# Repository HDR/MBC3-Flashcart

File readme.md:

# Make sure you read the [LICENSE](https://github.com/HDR/MBC3-Flashcart/blob/master/LICENSE)

MBC3 Flashcart based on retroreboot's cartridge that uses 0603 components (while based on the RetroReboot carts, these are completely redesigned from the ground up in kicad)

If you want a 4MB cart check out my new [MBC30 flashcart repo](https://github.com/HDR/MBC30-Flashcart)

Version 1.5 and beyond makes use of [djedditt's](https://github.com/djedditt/) [cartridge connector footprint](https://github.com/djedditt/kicad-gamepaks)

**PCBWay:**

As a disclaimer, i get 10% kickback on shared pcbway orders, if you want the cheaper option go with either JLCPCB or OshPark

If you want to support me for free (and get 5 USD in new user credit) you can use my PCBWay [Referral link](https://www.pcbway.com/setinvite.aspx?inviteid=388393) when signing up on PCBWay

**OSHPark:**

[Purchase on OSHPARK](https://oshpark.com/shared_projects/YCtVNv4A)

Make sure to select the "2 oz copper, 0.8mm thickness" option before checkout

**JLCPCB:**

Upload gerbers(.zip files) to [JLCPCB](http://jlcpcb.com)

Make sure you order with the following settings:

PCB Thickness: 0.8

PCB Color: Any

Surface Finish: ENIG-RoHS

Gold Fingers: Yes (45° chamfered border)

Castellated Holes: No

Check out the [Interactive BOM](https://hdr.github.io/ibom/MBC3-Flashcart) for an interactive website that lets you keep track of where everything goes.

## BOM

| Reference        | Part Number           | Description  | Package |
| :-------------: |:-------------:| :-----:| :-----:|
| U1 | AM29F016(2MB)/AM29F032(4MB)/MBM29F033C(4MB) | 2/4MB Flash Chip | TSOP-48/TSOP-40 |
| U2 | MBC3 | Get from real cartridge | LQFP-32 |
| U3 | FM18W08 | 256kbit FRAM | SOIC-28 |
| U4 | BA6129AF | Buy or get from real cartridge | SOIC-8 |
| U5 | [74LVC1G332GV,125](https://www.nexperia.com/products/analog-logic-ics/control-logic/gates/or-gates/74LVC1G332GV.html) | 3-input OR gate | TSOP-6 |
| C1 | [CL10B104KO8NNNC](https://lcsc.com/product-detail/Multilayer-Ceramic-Capacitors-MLCC-SMD-SMT_Samsung-Electro-Mechanics-CL10B104KO8NNNC_C66501.html)* | 100nF Capacitor | 0603 |
| C2 | [CL10B104KO8NNNC](https://lcsc.com/product-detail/Multilayer-Ceramic-Capacitors-MLCC-SMD-SMT_Samsung-Electro-Mechanics-CL10B104KO8NNNC_C66501.html)* | 100nF Capacitor | 0603 |
| C3 | [CL10B104KO8NNNC](https://lcsc.com/product-detail/Multilayer-Ceramic-Capacitors-MLCC-SMD-SMT_Samsung-Electro-Mechanics-CL10B104KO8NNNC_C66501.html)* | 100nF Capacitor | 0603 |
| C4 | [CL10C150JB8NNNC](https://lcsc.com/product-detail/Multilayer-Ceramic-Capacitors-MLCC-SMD-SMT_Samsung-Electro-Mechanics-CL10C150JB8NNNC_C1644.html)* | 15pF Capacitor | 0603 |
| C5 | [CL10C150JB8NNNC](https://lcsc.com/product-detail/Multilayer-Ceramic-Capacitors-MLCC-SMD-SMT_Samsung-Electro-Mechanics-CL10C150JB8NNNC_C1644.html)* | 15pF Capacitor | 0603 |
| C6 | [CL10B104KO8NNNC](https://lcsc.com/product-detail/Multilayer-Ceramic-Capacitors-MLCC-SMD-SMT_Samsung-Electro-Mechanics-CL10B104KO8NNNC_C66501.html)* | 100nF Capacitor | 0603 | 0603 |
| C7 | [CL10B104KO8NNNC](https://lcsc.com/product-detail/Multilayer-Ceramic-Capacitors-MLCC-SMD-SMT_Samsung-Electro-Mechanics-CL10B104KO8NNNC_C66501.html)* | 100nF Capacitor | 0603 |
| R1 | [RC0603FR-07330KL](https://lcsc.com/product-detail/Chip-Resistor-Surface-Mount_YAGEO-RC0603FR-07330KL_C114618.html)* | 330K Ω Resistor | 0603 |
| R2 | [RC0603FR-0710KL](https://lcsc.com/product-detail/Chip-Resistor-Surface-Mount_YAGEO-RC0603FR-0710KL_C98220.html)* | 10K Ω Resistor | 0603 |
| R3 | [RC0603FR-071KL](https://lcsc.com/product-detail/Chip-Resistor-Surface-Mount_YAGEO-RC0603FR-071KL_C22548.html)* | 1K Ω Resistor | 0603 |
| SW1 (Unmarked) | [K3-1296S-E1](https://lcsc.com/product-detail/Slide-Switches_Korean-Hroparts-Elec-K3-1296S-E1_C128955.html)** | SPDT Switch | N/A |
| X1 | R26-32.768-12.5-10PPM | 32.768 kHz Crystal | N/A |
| Batt CR2025 | BK-6219-TR | CR2025 Coin Cell Retainer | N/A |

*Linked Capacitors/Resistors are suggestions, use whatever matches the ratings and package.
**Switch is optional, and is only used with 4MB chips.

## Changelog:

**1.2:**
- Fixed missing traces

**1.3:**
- Fixed some trace issues with Y1
- Rerouted the pcb entirely

**1.4:**
- Fixed a short between A16 and VCC

**1.4.1:**
- Changed AM29F016 footprint to make chip alignment easier
- Cleaned up traces (visual)

**1.5:**
- Updated kicad version from 5 to 6.0
- Redrew outline to be a closer match to original
- Added markings to make cart look more original
- Added switch for 2x2mb mode (this means the cart can store 2 separate roms, saves are still shared)
- Changed footprint designators
- Added test pads
- Added date marking
- Relocated alignment holes for a better fit

## Images

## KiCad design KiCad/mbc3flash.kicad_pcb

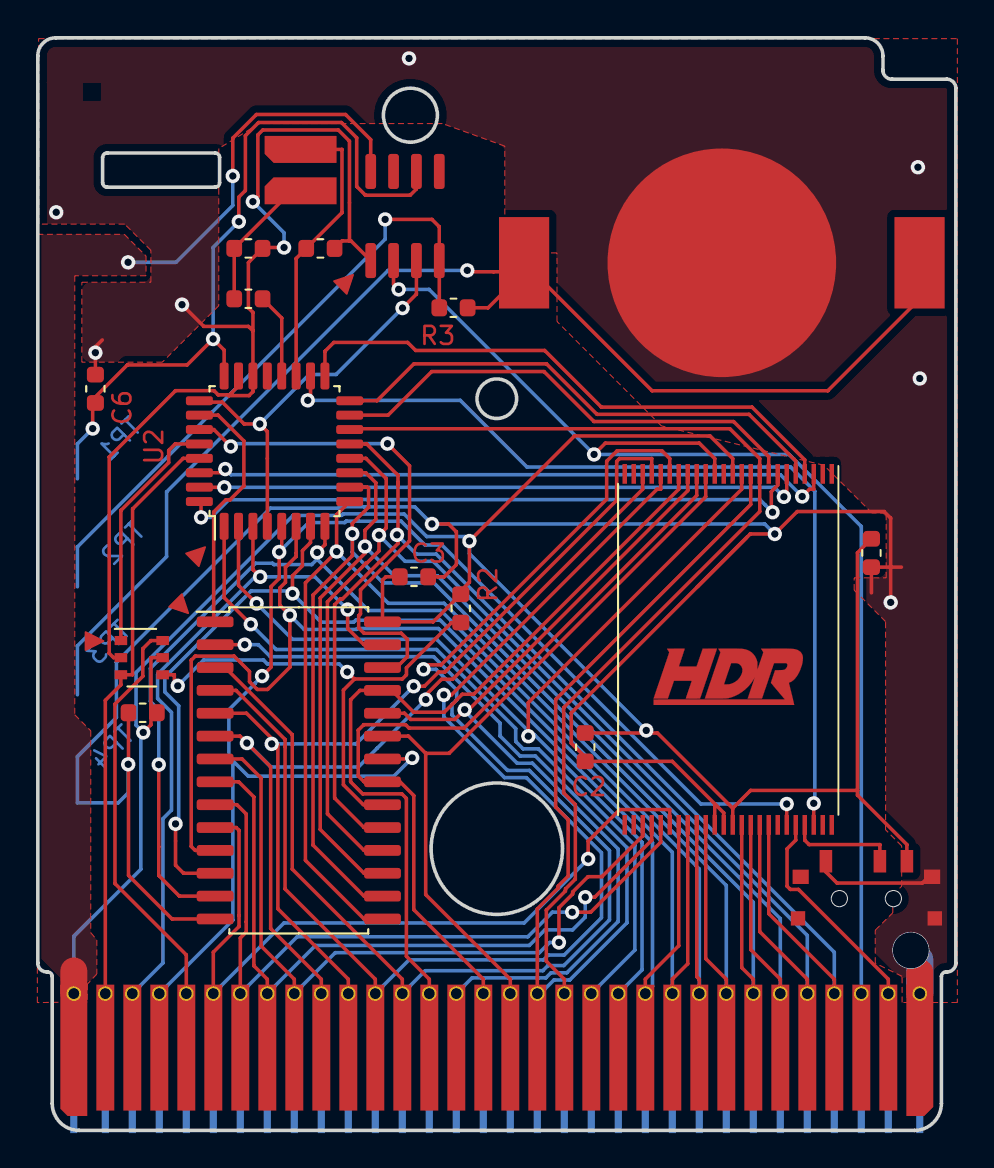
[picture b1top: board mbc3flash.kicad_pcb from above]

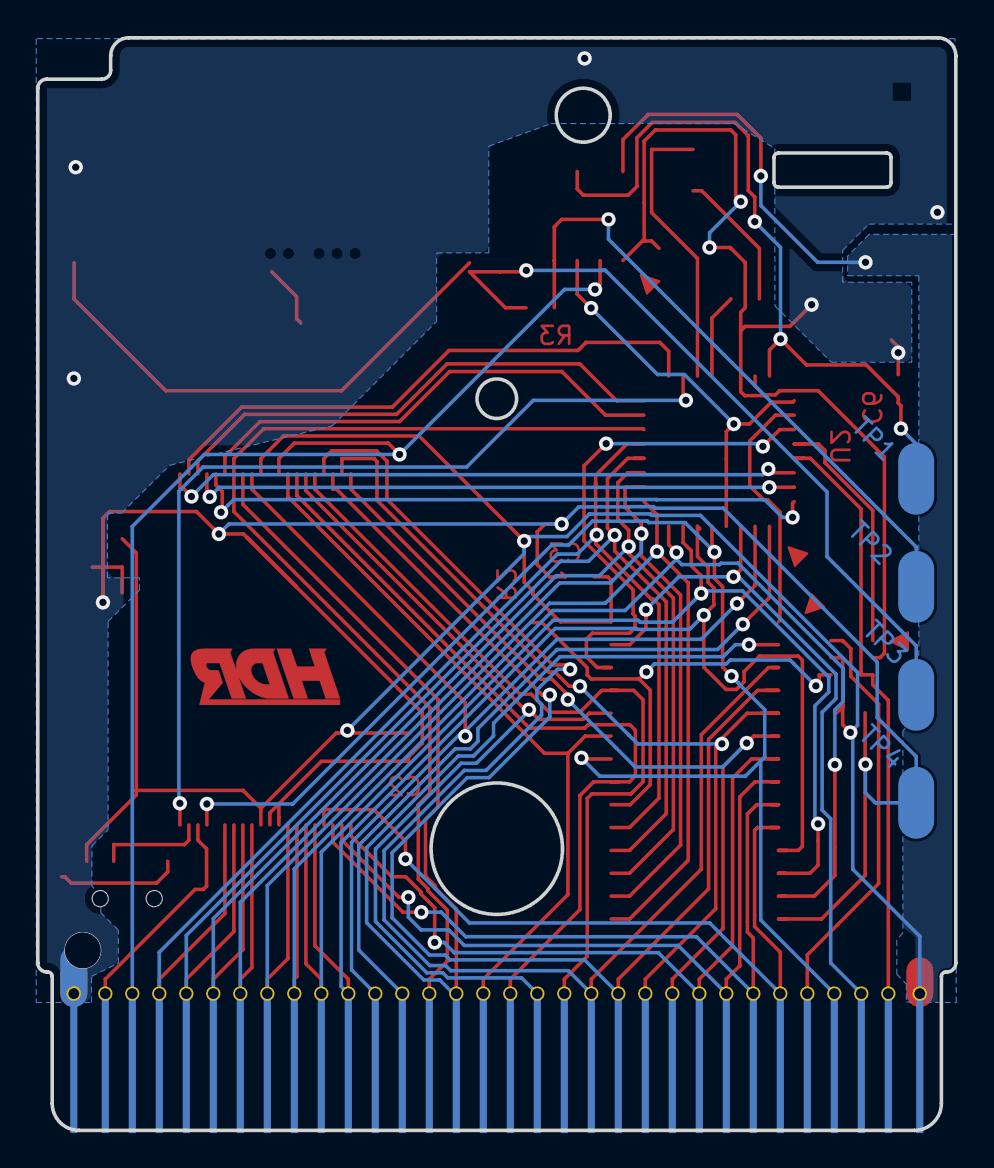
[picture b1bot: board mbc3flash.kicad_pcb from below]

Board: 2 copper layers, 51.0 x 60.7 mm, 25 parts (5 on the bottom side), 51 nets.

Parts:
B1: Battery_Cell; BK-6219-TR
C1, C2, C3, C6, C7: 0.1 uF; C_0603_1608Metric
C4, C5: 15 pF; C_0603_1608Metric
GNDPAD1: Nintendo_3x3_GNDPad
PAD*: GBA-ProductionIndicator
R1: 300Kohm; R_0603_1608Metric
R2: 10 Kohm; R_0603_1608Metric
R3: 1 Kohm; R_0603_1608Metric
SW1: SW_SPDT; SW_SPDT-K3-1296S-E1
TP1: RTC_VOUT; GameBoy_Testpoint
TP2: Battery_Positive_After_Resistor; GameBoy_Testpoint
TP3: Battery_Positive; GameBoy_Testpoint
TP4: Ground; GameBoy_Testpoint
U0: CartBus; GameBoy_GamePak_CGB-002_P1.50mm_Edge
U1: AM29F016; TSOP-I-48_18.4x12mm_P0.5mm
U2: MBC3
U3: FM18W08; SOIC-28W_7.5x17.9mm_P1.27mm
U4: BA6129AF; SOIC-8_3.9x4.9mm_P1.27mm
U5: 74LVC1G332GW,125; TSOP-6_1.65x3.05mm_P0.95mm
Y1: Crystal; Resonator_SMD_muRata_CDSCB-2pin_4.5x2.0mm_HandSoldering

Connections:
#CE: R2.1, U3.20, U5.4
A0: U0.6, U1.30, U3.10
A1: U0.7, U1.29, U3.9
A2: U0.8, U1.28, U3.8
A3: U0.9, U1.27, U3.7
A4: U0.10, U1.22, U3.6
A5: U0.11, U1.21, U3.5
A6: U0.12, U1.20, U3.4
A7: U0.13, U1.19, U3.3
A8: U0.14, U1.18, U3.25
A9: U0.15, U1.17, U3.24
A10: U0.16, U1.16, U3.21
A11: U0.17, U1.15, U3.23
A12: U0.18, U1.10, U3.2
A13: U0.19, U1.9, U2.14
A14: U0.20, U2.1
A15: U0.21, U1.11, U2.2
AA13: U2.27, U3.26
AA14: U2.26, U3.1
BT+: B1.1, R3.1, TP3.1
CLK: U0.2, U2.29, U5.3
CS: U0.5, U5.6
D0: U0.22, U1.31, U2.6, U3.11
D1: U0.23, U1.32, U2.7, U3.12
D2: U0.24, U1.33, U2.8, U3.13
D3: U0.25, U1.34, U2.9, U3.15
D4: U0.26, U1.38, U2.10, U3.16
D5: U0.27, U1.39, U2.11, U3.17
D6: U0.28, U1.40, U2.12, U3.18
D7: U0.29, U1.41, U2.13, U3.19
GND: B1.2, C1.1, C2.2, C3.1, C4.2, C5.1, C6.2, C7.1, SW1.1, TP4.1, U0.32, U1.35, U1.36, U2.22, U2.23, U3.14, U4.1, U5.2
unnamed: C5.2, R1.2, Y1.1
unnamed: SW1.2, U1.45
PWR: C6.1, TP1.1, U2.24, U4.6
RA14: U1.8, U2.15
RA15: U1.7, U2.32
RA16: U1.6, U2.31
RA17: U1.5, U2.16
RA18: U1.4, U2.17
RA19: U1.3, U2.30
RA20: U1.46, U2.18
RESET: U0.30, U1.14, U4.2
VCC: C1.2, C2.1, C3.2, C7.2, R2.2, SW1.3, U0.1, U1.12, U1.37, U3.28, U4.8, U5.5
Vbatt: R3.2, TP2.1, U4.4
WE_AUD: U0.31, U1.44
XIN: C4.1, U2.19, Y1.2
XOUT: R1.1, U2.20
\RAMCS: U2.28, U5.1
\RD: U0.4, U1.43, U2.5, U3.22
\RST: U2.4, U2.25, U4.3
\WR: U0.3, U2.3, U3.27

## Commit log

2019-02-19 commit readme
2019-03-01 Add files and update readme
2019-03-17 Update oshpark project link
2019-03-17 Update pictures and readme
2019-03-29 2.2
    - Re organized some stuff
2019-03-29 2.2
    Update images
2019-07-03 Redesigned carts from the ground up
    The original commits to this repo used modified versions of the
    original, as of this commit the carts are designed in Kicad from the
    ground up.
2019-07-14 1.3
    - Fixed some issues with the traces around Y1
    - Rerouted PCB
2019-08-16 1.4
    - Fixed a short between A16 and VCC
2019-10-28 Update links
2019-11-05 1.4.1
2020-05-22 Add kicad files
    Finally got around to cleaning up the project folder enough for it to be in a releaseable state.
2020-05-22 Add missing libs
2022-02-03 Release 1.5
    - Updated kicad version from 5 to 6.0
    - Redrew outline to be a closer match to original
    - Added markings to make cart look more original
    - Added switch for 2x2mb mode (this means the cart can store 2 separate roms, saves are still shared)
    - Changed footprint designators
    - Added test pads
2022-05-27 Update Gerbers for JLCPCB
    JLC expects some specific settings to correctly render gerber files
2022-09-16 Add Licence
